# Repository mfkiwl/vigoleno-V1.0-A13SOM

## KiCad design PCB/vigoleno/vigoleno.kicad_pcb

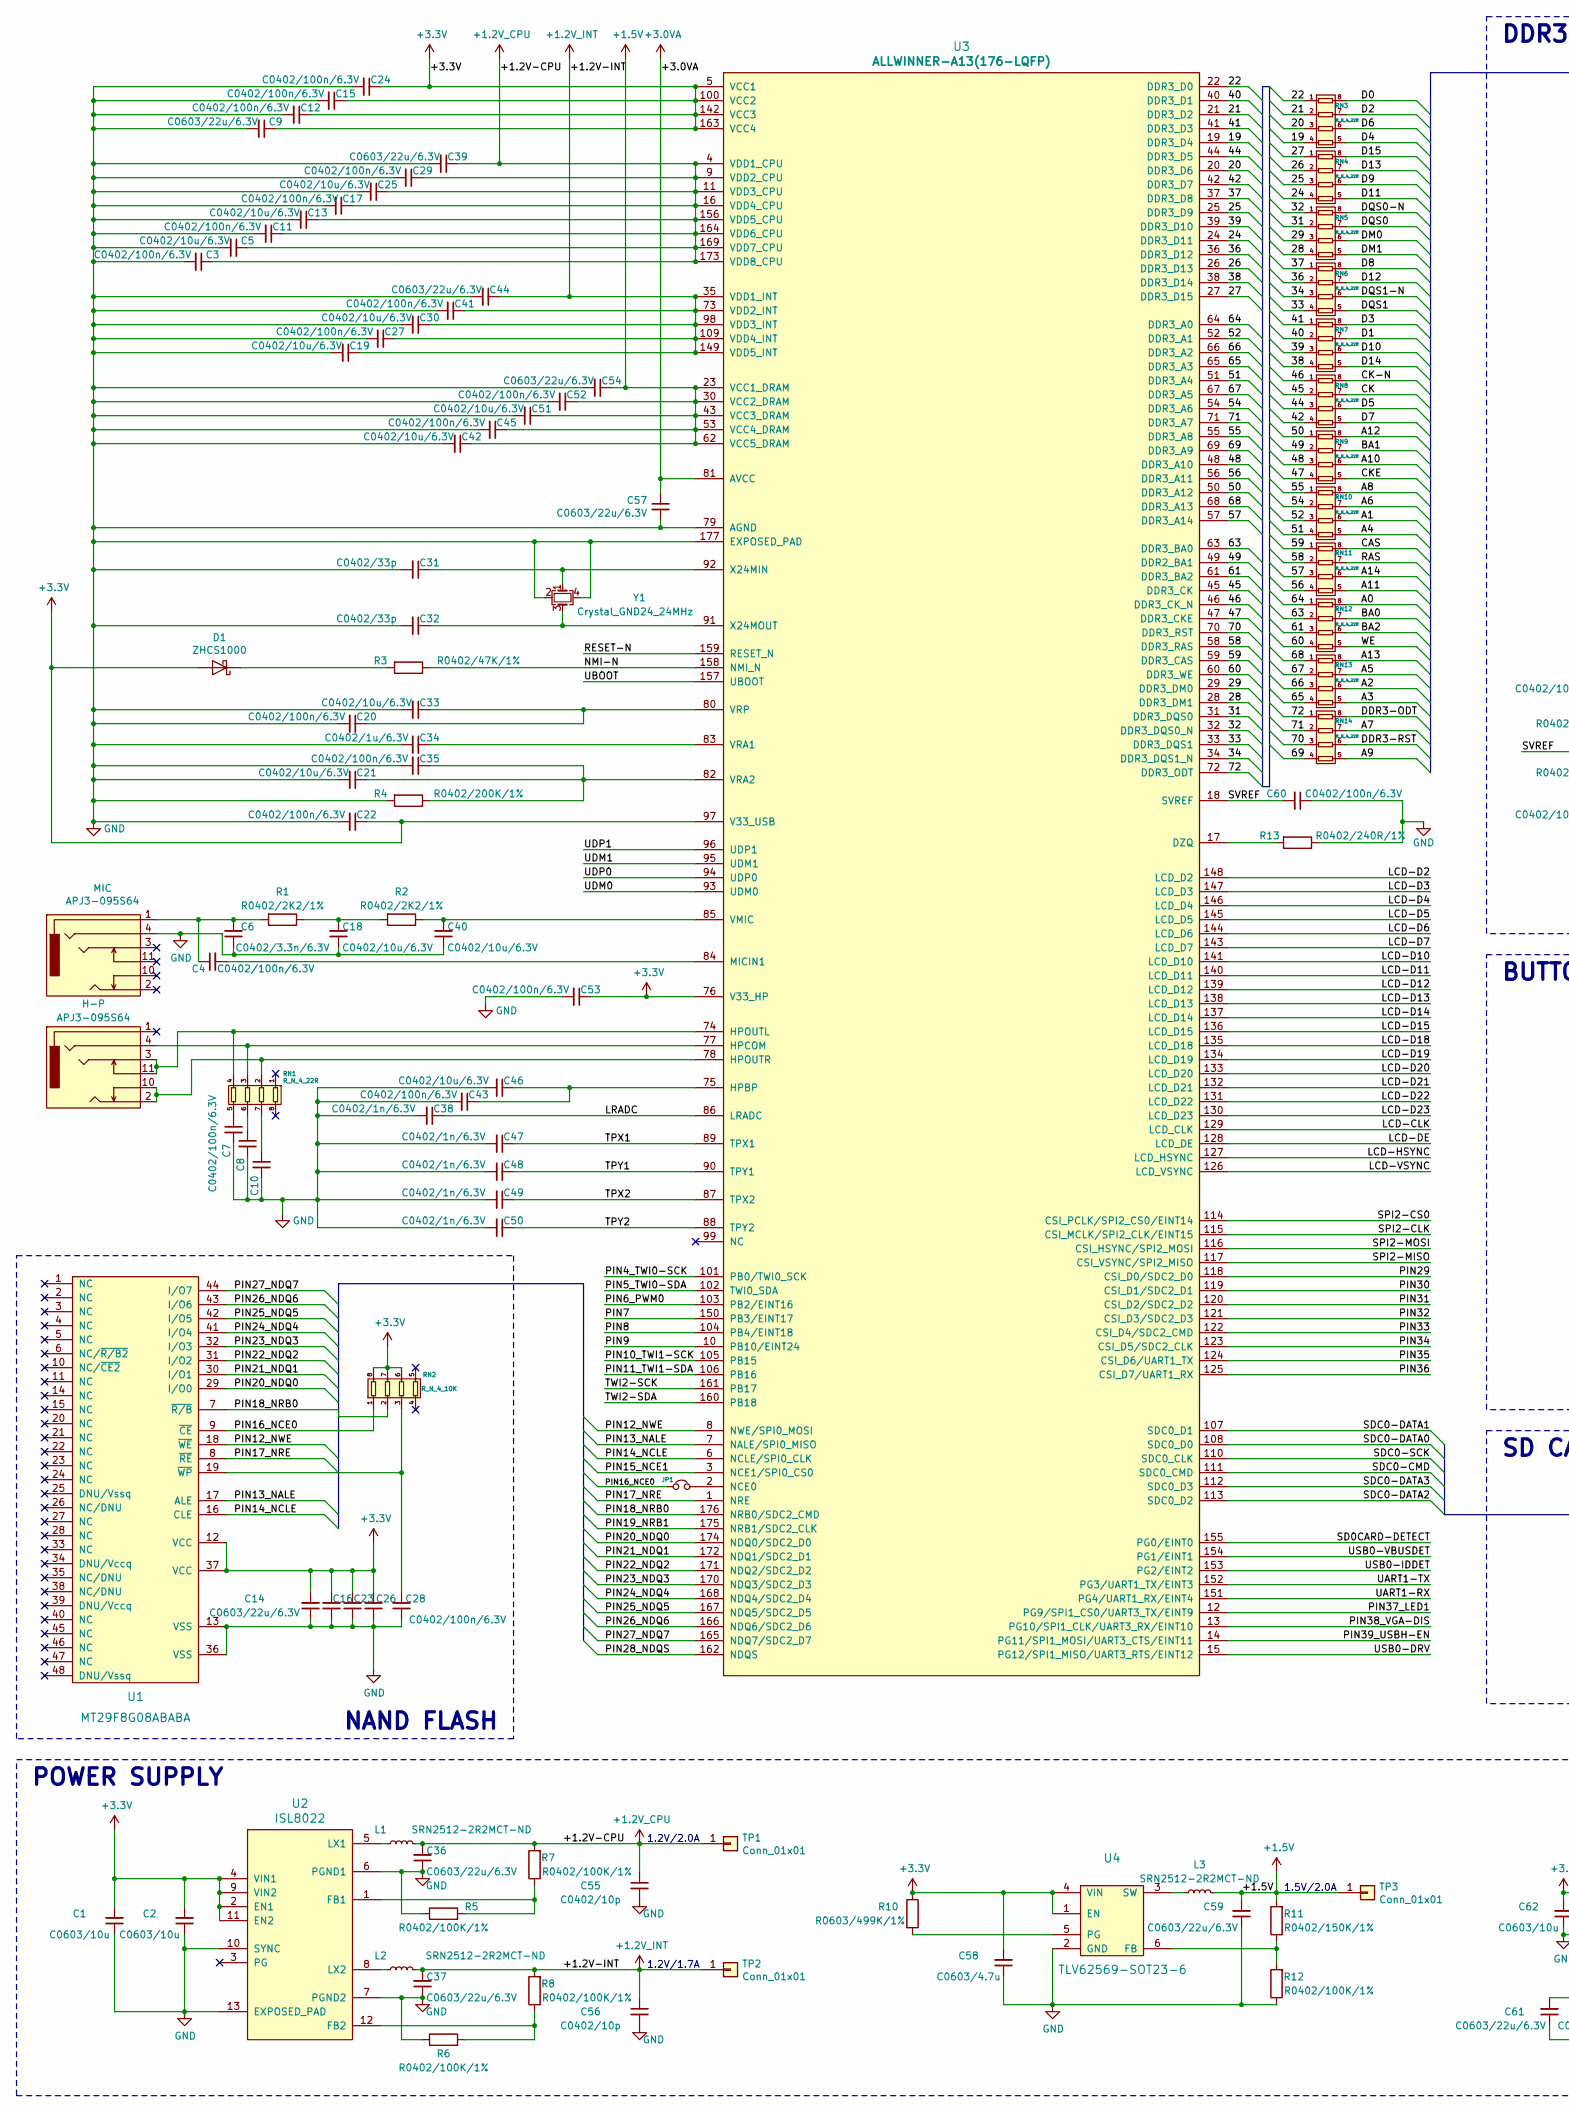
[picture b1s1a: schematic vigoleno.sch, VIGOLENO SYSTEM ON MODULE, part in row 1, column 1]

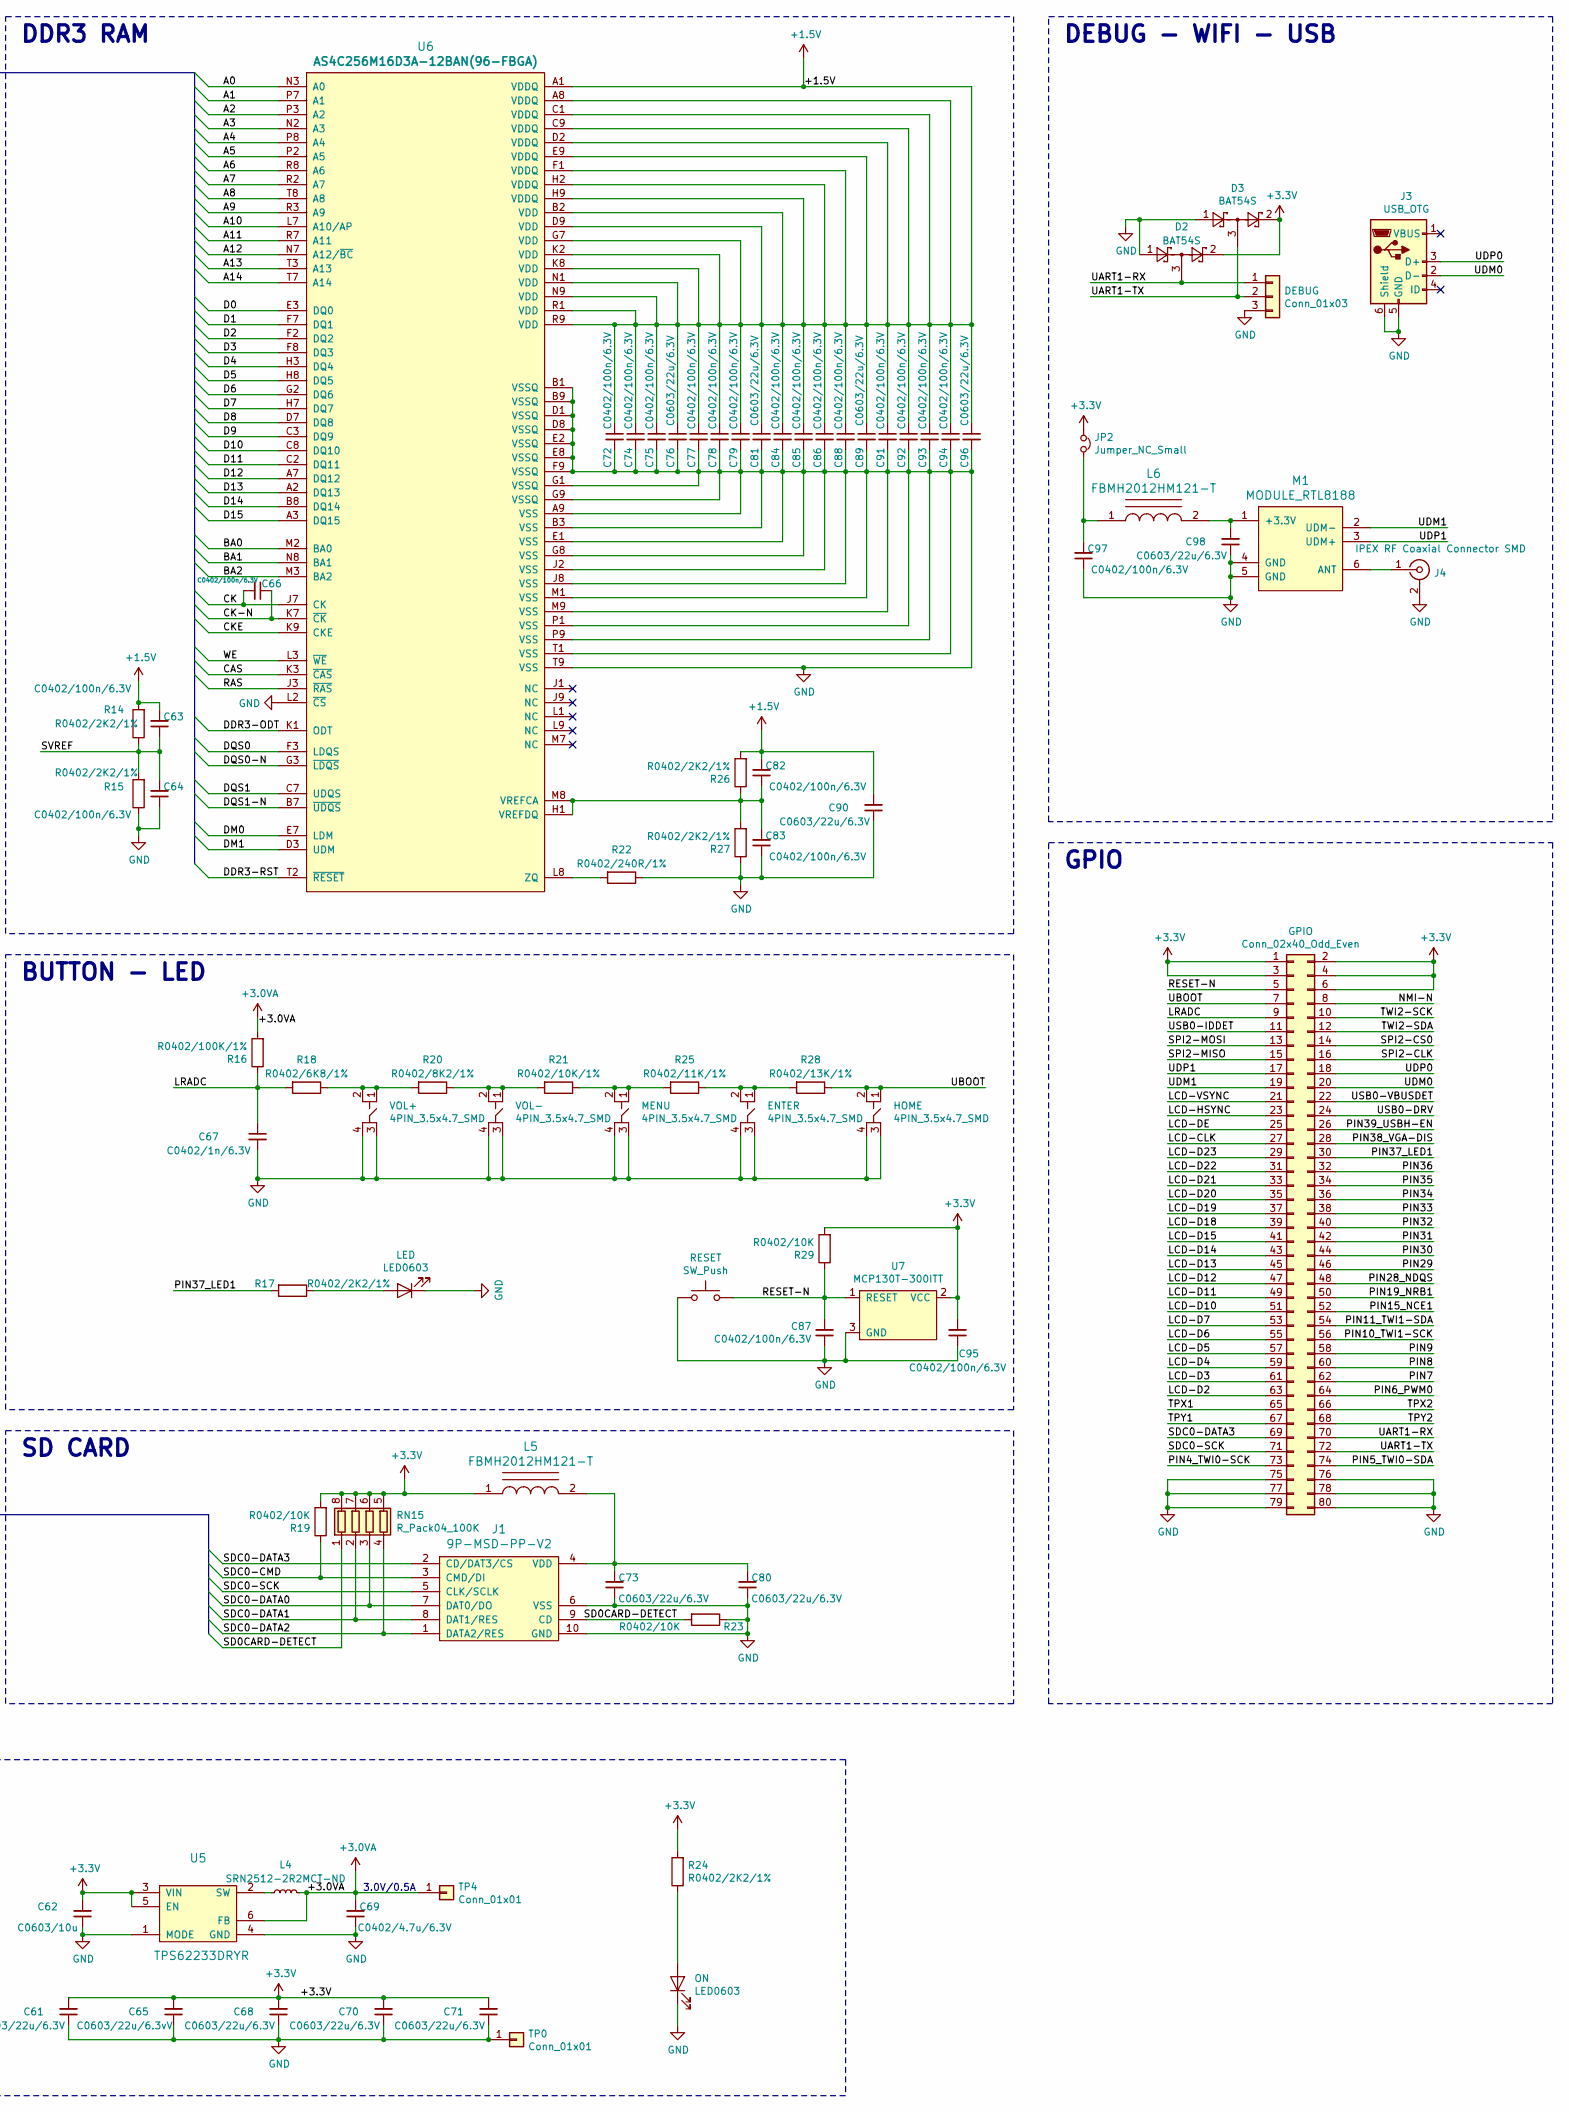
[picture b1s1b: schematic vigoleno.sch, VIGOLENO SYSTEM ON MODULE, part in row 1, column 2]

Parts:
C1, C2, C62: C0603/10u; C0603_HandSoldering
C3, C4, C7, C8, C10, C11, C12, C15, C16, C17, C20, C22, C23, C24, C26, C27, C28, C29, C35, C41, C43, C45, C52, C53, C60, C63, C64, C66, C72, C74, C75, C77, C78, C79, C82, C83, C84, C85, C86, C87, C88, C91, C92, C93, C94, C95, C97: C0402/100n/6.3V; C0402_HandSoldering
C5, C13, C18, C19, C21, C25, C30, C33, C40, C42, C46, C51: C0402/10u/6.3V; C0402_HandSoldering
C6: C0402/3.3n/6.3V; C0402_HandSoldering
C9, C14, C36, C37, C39, C44, C54, C57, C59, C61, C68, C70, C71, C73, C76, C80, C81, C89, C90, C96, C98: C0603/22u/6.3V; C0603_HandSoldering
C31, C32: C0402/33p; C0402_HandSoldering
C34: C0402/1u/6.3V; C0402_HandSoldering
C38, C47, C48, C49, C50, C67: C0402/1n/6.3V; C0402_HandSoldering
C55, C56: C0402/10p; C0402_HandSoldering
C58: C0603/4.7u; C0603_HandSoldering
C65: C0603/22u/6.3vV; C0603_HandSoldering
C69: C0402/4.7u/6.3V; C0402_HandSoldering
D1: ZHCS1000; SOT-23
D2, D3: BAT54S; SOT-23
DEBUG: Conn_01x03; Molex_CLIK-Mate_502585-0370_1x03-1MP_P1.50mm_Horizontal
ENTER: 4PIN_3.5x4.7_SMD
GPIO: Conn_02x40_Odd_Even; 2x40_pitch 0.8mm_SMD_header
H-P: APJ3-095S64; APJ3-095S64(Board_Cutout)
HOME: 4PIN_3.5x4.7_SMD
J1: 9P-MSD-PP-V2; MicroSD_9Pin_MSD-PP-V2
J3: USB_OTG; USB_Micro_3MV2
J4: IPEX RF Coaxial Connector SMD; U.FL_Hirose_U.FL-R-SMT-1_Vertical
JP1, JP2: Jumper_NC_Small; SolderJumper-2_P1.3mm_Open_TrianglePad1.0x1.5mm
L1, L2, L3, L4: SRN2512-2R2MCT-ND; Inductor_SRN2512_Series
L5, L6: FBMH2012HM121-T; L_0805_2012Metric
LED: LED0603; LED_0603_1608Metric
M1: MODULE_RTL8188; RTL8188_MODULE
MENU: 4PIN_3.5x4.7_SMD
MIC: APJ3-095S64; APJ3-095S64(Board_Cutout)
ON: LED0603; LED_0603_1608Metric
R1, R2, R14, R15, R17, R24, R26, R27: R0402/2K2/1%; R0402_HandSoldering
R3: R0402/47K/1%; R0402_HandSoldering
R4: R0402/200K/1%; R0402_HandSoldering
R5, R6, R7, R8, R12, R16: R0402/100K/1%; R0402_HandSoldering
R10: R0603/499K/1%; R0603_HandSoldering
R11: R0402/150K/1%; R0402_HandSoldering
R13, R22: R0402/240R/1%; R0402_HandSoldering
R18: R0402/6K8/1%; R0402_HandSoldering
R19, R23, R29: R0402/10K; R0402_HandSoldering
R20: R0402/8K2/1%; R0402_HandSoldering
R21: R0402/10K/1%; R0402_HandSoldering
R25: R0402/11K/1%; R0402_HandSoldering
R28: R0402/13K/1%; R0402_HandSoldering
RESET: SW_Push; SW_3x6x5_2Pin_SMD
RN1, RN3, RN4, RN5, RN6, RN7, RN8, RN9, RN10, RN11, RN12, RN13, RN14: R_N_4_22R; R_Array_0804_Convex_4x0402
RN2: R_N_4_10K; R_Array_0804_Convex_4x0402
RN15: R_Pack04_100K; R_Array_Convex_4x0603
TP0, TP1, TP2, TP3, TP4: Conn_01x01; TestPoint_Pad_D1.0mm
U1: MT29F8G08ABABA; S34ML08G2(48-TSOP)
U2: ISL8022; DFN-12-1EP_3x4mm_P0.5mm_EP1.7x3.3mm
U3: ALLWINNER-A13(176-LQFP); AllWinner-A13(176-LQFP)
U4: TLV62569-SOT23-6; SOT-23-6
U5: TPS62233DRYR; TPS62233DRYR_6_UFDFN
U6: AS4C256M16D3A-12BAN(96-FBGA)
U7: MCP130T-300ITT; SOT-23
VOL+: 4PIN_3.5x4.7_SMD
VOL-: 4PIN_3.5x4.7_SMD
Y1: Crystal_GND24_24MHz; Crystal_SMD_SeikoEpson_TSX3225-4pin_3.2x2.5mm_HandSoldering

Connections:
+3V3: C1.2, C2.2, C9.1, C12.1, C14.2, C15.1, C16.2, C22.1, C23.2, C24.1, C26.2, C53.1, C58.2, C61.2, C62.2, C65.2, C68.2, C70.2, C71.2, C95.2, D1.1 (A), D2.2, D3.2, GPIO.1, GPIO.2, GPIO.3, GPIO.4, GPIO.6, JP2.1, L5.1, R10.1, R19.2, R24.2, R29.2, RN2.6, RN2.7, RN2.8, RN15.5 (R4.2), RN15.6 (R3.2), RN15.7 (R2.2), RN15.8 (R1.2), U1.12 (VCC), U1.37 (VCC), U2.2 (EN1), U2.4 (VIN1), U2.9 (VIN2), U2.11 (EN2), U3.5 (VCC1), U3.76 (V33_HP), U3.97 (V33_USB), U3.100 (VCC2), U3.142 (VCC3), U3.163 (VCC4), U4.1 (EN), U4.4 (VIN), U5.3 (VIN), U5.5 (EN), U7.2 (VCC)
/19: RN3.4, U3.19 (DDR3_D4)
/20: RN3.3, U3.20 (DDR3_D6)
/21: RN3.2, U3.21 (DDR3_D2)
/22: RN3.1, U3.22 (DDR3_D0)
/24: RN4.4, U3.24 (DDR3_D11)
/25: RN4.3, U3.25 (DDR3_D9)
/26: RN4.2, U3.26 (DDR3_D13)
/27: RN4.1, U3.27 (DDR3_D15)
/28: RN5.4, U3.28 (DDR3_DM1)
/29: RN5.3, U3.29 (DDR3_DM0)
/31: RN5.2, U3.31 (DDR3_DQS0)
/32: RN5.1, U3.32 (DDR3_DQS0_N)
/33: RN6.4, U3.33 (DDR3_DQS1)
/34: RN6.3, U3.34 (DDR3_DQS1_N)
/36: RN6.2, U3.36 (DDR3_D12)
/37: RN6.1, U3.37 (DDR3_D8)
/38: RN7.4, U3.38 (DDR3_D14)
/39: RN7.3, U3.39 (DDR3_D10)
/40: RN7.2, U3.40 (DDR3_D1)
/41: RN7.1, U3.41 (DDR3_D3)
/42: RN8.4, U3.42 (DDR3_D7)
/44: RN8.3, U3.44 (DDR3_D5)
/45: RN8.2, U3.45 (DDR3_CK)
/46: RN8.1, U3.46 (DDR3_CK_N)
/47: RN9.4, U3.47 (DDR3_CKE)
/48: RN9.3, U3.48 (DDR3_A10)
/49: RN9.2, U3.49 (DDR2_BA1)
/50: RN9.1, U3.50 (DDR3_A12)
/51: RN10.4, U3.51 (DDR3_A4)
/52: RN10.3, U3.52 (DDR3_A1)
/54: RN10.2, U3.54 (DDR3_A6)
/55: RN10.1, U3.55 (DDR3_A8)
/56: RN11.4, U3.56 (DDR3_A11)
/57: RN11.3, U3.57 (DDR3_A14)
/58: RN11.2, U3.58 (DDR3_RAS)
/59: RN11.1, U3.59 (DDR3_CAS)
/60: RN12.4, U3.60 (DDR3_WE)
/61: RN12.3, U3.61 (DDR3_BA2)
/63: RN12.2, U3.63 (DDR3_BA0)
/64: RN12.1, U3.64 (DDR3_A0)
/65: RN13.4, U3.65 (DDR3_A3)
/66: RN13.3, U3.66 (DDR3_A2)
/67: RN13.2, U3.67 (DDR3_A5)
/68: RN13.1, U3.68 (DDR3_A13)
/69: RN14.4, U3.69 (DDR3_A9)
/70: RN14.3, U3.70 (DDR3_RST)
/71: RN14.2, U3.71 (DDR3_A7)
/72: RN14.1, U3.72 (DDR3_ODT)
/+1.2V-CPU: C3.1, C5.1, C11.1, C13.1, C17.1, C25.1, C29.1, C36.2, C39.1, C55.1, L1.2, R7.2, TP1.1, U3.4 (VDD1_CPU), U3.9 (VDD2_CPU), U3.11 (VDD3_CPU), U3.16 (VDD4_CPU), U3.156 (VDD5_CPU), U3.164 (VDD6_CPU), U3.169 (VDD7_CPU), U3.173 (VDD8_CPU)
/+1.2V-INT: C19.1, C27.1, C30.1, C37.2, C41.1, C44.1, C56.1, L2.2, R8.2, TP2.1, U3.35 (VDD1_INT), U3.73 (VDD2_INT), U3.98 (VDD3_INT), U3.109 (VDD4_INT), U3.149 (VDD5_INT)
/+3.0VA: C57.1, C69.2, L4.2, R16.2, TP4.1, U3.81 (AVCC), U5.6 (FB)
/A0: RN12.8, U6.N3 (A0)
/A1: RN10.6, U6.P7 (A1)
/A2: RN13.6, U6.P3 (A2)
/A3: RN13.5, U6.N2 (A3)
/A4: RN10.5, U6.P8 (A4)
/A5: RN13.7, U6.P2 (A5)
/A6: RN10.7, U6.R8 (A6)
/A7: RN14.7, U6.R2 (A7)
/A8: RN10.8, U6.T8 (A8)
/A9: RN14.5, U6.R3 (A9)
/A10: RN9.6, U6.L7 (A10/AP)
/A11: RN11.5, U6.R7 (A11)
/A12: RN9.8, U6.N7 (A12/~BC)
/A13: RN13.8, U6.T3 (A13)
/A14: RN11.6, U6.T7 (A14)
/BA0: RN12.7, U6.M2 (BA0)
/BA1: RN9.7, U6.N8 (BA1)
/BA2: RN12.6, U6.M3 (BA2)
/CAS: RN11.8, U6.K3 (~CAS)
/CK: C66.2, RN8.7, U6.J7 (CK)
/CK-N: C66.1, RN8.8, U6.K7 (~CK)
/CKE: RN9.5, U6.K9 (CKE)
/D0: RN3.8, U6.E3 (DQ0)
/D1: RN7.7, U6.F7 (DQ1)
/D2: RN3.7, U6.F2 (DQ2)
/D3: RN7.8, U6.F8 (DQ3)
/D4: RN3.5, U6.H3 (DQ4)
/D5: RN8.6, U6.H8 (DQ5)
/D6: RN3.6, U6.G2 (DQ6)
/D7: RN8.5, U6.H7 (DQ7)
/D8: RN6.8, U6.D7 (DQ8)
/D9: RN4.6, U6.C3 (DQ9)
/D10: RN7.6, U6.C8 (DQ10)
/D11: RN4.5, U6.C2 (DQ11)
/D12: RN6.7, U6.A7 (DQ12)
/D13: RN4.7, U6.A2 (DQ13)
/D14: RN7.5, U6.B8 (DQ14)
/D15: RN4.8, U6.A3 (DQ15)
/DDR3-ODT: RN14.8, U6.K1 (ODT)
/DDR3-RST: RN14.6, U6.T2 (~RESET)
/DM0: RN5.6, U6.E7 (LDM)
/DM1: RN5.5, U6.D3 (UDM)
/DQS0: RN5.7, U6.F3 (LDQS)
/DQS0-N: RN5.8, U6.G3 (~LDQS)
/DQS1: RN6.5, U6.C7 (UDQS)
/DQS1-N: RN6.6, U6.B7 (~UDQS)
/LCD-CLK: GPIO.27, U3.129 (LCD_CLK)
/LCD-D2: GPIO.63, U3.148 (LCD_D2)
/LCD-D3: GPIO.61, U3.147 (LCD_D3)
/LCD-D4: GPIO.59, U3.146 (LCD_D4)
/LCD-D5: GPIO.57, U3.145 (LCD_D5)
/LCD-D6: GPIO.55, U3.144 (LCD_D6)
/LCD-D7: GPIO.53, U3.143 (LCD_D7)
/LCD-D10: GPIO.51, U3.141 (LCD_D10)
/LCD-D11: GPIO.49, U3.140 (LCD_D11)
/LCD-D12: GPIO.47, U3.139 (LCD_D12)
/LCD-D13: GPIO.45, U3.138 (LCD_D13)
/LCD-D14: GPIO.43, U3.137 (LCD_D14)
/LCD-D15: GPIO.41, U3.136 (LCD_D15)
/LCD-D18: GPIO.39, U3.135 (LCD_D18)
/LCD-D19: GPIO.37, U3.134 (LCD_D19)
/LCD-D20: GPIO.35, U3.133 (LCD_D20)
/LCD-D21: GPIO.33, U3.132 (LCD_D21)
/LCD-D22: GPIO.31, U3.131 (LCD_D22)
/LCD-D23: GPIO.29, U3.130 (LCD_D23)
/LCD-DE: GPIO.25, U3.128 (LCD_DE)
/LCD-HSYNC: GPIO.23, U3.127 (LCD_HSYNC)
/LCD-VSYNC: GPIO.21, U3.126 (LCD_VSYNC)
/LRADC: C38.1, C67.1, GPIO.9, R16.1, R18.2, U3.86 (LRADC)
/NMI-N: GPIO.8, R3.1, U3.158 (NMI_N)
/PIN4_TWI0-SCK: GPIO.73, U3.101 (PB0/TWI0_SCK)
/PIN5_TWI0-SDA: GPIO.74, U3.102 (TWI0_SDA)
/PIN6_PWM0: GPIO.64, U3.103 (PB2/EINT16)
/PIN7: GPIO.62, U3.150 (PB3/EINT17)
/PIN8: GPIO.60, U3.104 (PB4/EINT18)
/PIN9: GPIO.58, U3.10 (PB10/EINT24)
/PIN10_TWI1-SCK: GPIO.56, U3.105 (PB15)
/PIN11_TWI1-SDA: GPIO.54, U3.106 (PB16)
/PIN12_NWE: U1.18 (~WE), U3.8 (NWE/SPI0_MOSI)
/PIN13_NALE: U1.17 (ALE), U3.7 (NALE/SPI0_MISO)
/PIN14_NCLE: U1.16 (CLE), U3.6 (NCLE/SPI0_CLK)
/PIN15_NCE1: GPIO.52, U3.3 (NCE1/SPI0_CS0)
/PIN16_NCE0: JP1.1, RN2.1, U1.9 (~CE)
/PIN17_NRE: U1.8 (~RE), U3.1 (NRE)
/PIN18_NRB0: RN2.2, U1.7 (~R/B), U3.176 (NRB0/SDC2_CMD)
/PIN19_NRB1: GPIO.50, U3.175 (NRB1/SDC2_CLK)
/PIN20_NDQ0: U1.29 (I/O0), U3.174 (NDQ0/SDC2_D0)
/PIN21_NDQ1: U1.30 (I/O1), U3.172 (NDQ1/SDC2_D1)
/PIN22_NDQ2: U1.31 (I/O2), U3.171 (NDQ2/SDC2_D2)
/PIN23_NDQ3: U1.32 (I/O3), U3.170 (NDQ3/SDC2_D3)
/PIN24_NDQ4: U1.41 (I/O4), U3.168 (NDQ4/SDC2_D4)
/PIN25_NDQ5: U1.42 (I/O5), U3.167 (NDQ5/SDC2_D5)
/PIN26_NDQ6: U1.43 (I/O6), U3.166 (NDQ6/SDC2_D6)
/PIN27_NDQ7: U1.44 (I/O7), U3.165 (NDQ7/SDC2_D7)
/PIN28_NDQS: GPIO.48, U3.162 (NDQS)
/PIN29: GPIO.46, U3.118 (CSI_D0/SDC2_D0)
/PIN30: GPIO.44, U3.119 (CSI_D1/SDC2_D1)
/PIN31: GPIO.42, U3.120 (CSI_D2/SDC2_D2)
/PIN32: GPIO.40, U3.121 (CSI_D3/SDC2_D3)
/PIN33: GPIO.38, U3.122 (CSI_D4/SDC2_CMD)
/PIN34: GPIO.36, U3.123 (CSI_D5/SDC2_CLK)
/PIN35: GPIO.34, U3.124 (CSI_D6/UART1_TX)
/PIN36: GPIO.32, U3.125 (CSI_D7/UART1_RX)
/PIN37_LED1: GPIO.30, R17.2, U3.12 (PG9/SPI1_CS0/UART3_TX/EINT9)
/PIN38_VGA-DIS: GPIO.28, U3.13 (PG10/SPI1_CLK/UART3_RX/EINT10)
/PIN39_USBH-EN: GPIO.26, U3.14 (PG11/SPI1_MOSI/UART3_CTS/EINT11)
/RAS: RN11.7, U6.J3 (~RAS)
/RESET-N: C87.2, GPIO.5, R29.1, RESET.2, U3.159 (RESET_N), U7.1 (RESET)
/SD0CARD-DETECT: J1.9 (CD), R23.2, RN15.1 (R1.1), U3.155 (PG0/EINT0)
/SDC0-CMD: J1.3 (CMD/DI), R19.1, U3.111 (SDC0_CMD)
/SDC0-DATA0: J1.7 (DAT0/DO), RN15.3 (R3.1), U3.108 (SDC0_D0)
/SDC0-DATA1: J1.8 (DAT1/RES), RN15.2 (R2.1), U3.107 (SDC0_D1)
/SDC0-DATA2: J1.1 (DATA2/RES), RN15.4 (R4.1), U3.113 (SDC0_D2)
/SDC0-DATA3: GPIO.69, J1.2 (CD/DAT3/CS), U3.112 (SDC0_D3)
/SDC0-SCK: GPIO.71, J1.5 (CLK/SCLK), U3.110 (SDC0_CLK)
/SPI2-CLK: GPIO.16, U3.115 (CSI_MCLK/SPI2_CLK/EINT15)
/SPI2-CS0: GPIO.14, U3.114 (CSI_PCLK/SPI2_CS0/EINT14)
/SPI2-MISO: GPIO.15, U3.117 (CSI_VSYNC/SPI2_MISO)
/SPI2-MOSI: GPIO.13, U3.116 (CSI_HSYNC/SPI2_MOSI)
/SVREF: C60.2, C63.1, C64.2, R14.1, R15.2, U3.18 (SVREF)
/TPX1: C47.1, GPIO.65, U3.89 (TPX1)
/TPX2: C49.1, GPIO.66, U3.87 (TPX2)
/TPY1: C48.1, GPIO.67, U3.90 (TPY1)
/TPY2: C50.1, GPIO.68, U3.88 (TPY2)
/TWI2-SCK: GPIO.10, U3.161 (PB17)
/TWI2-SDA: GPIO.12, U3.160 (PB18)
/UART1-RX: D2.3, DEBUG.1, GPIO.70, U3.151 (PG4/UART1_RX/EINT4)
/UART1-TX: D3.3, DEBUG.2, GPIO.72, U3.152 (PG3/UART1_TX/EINT3)
/UBOOT: GPIO.7, HOME.1 (A), HOME.2 (B), R28.1, U3.157 (UBOOT)
/UDM0: GPIO.20, J3.2 (D-), U3.93 (UDM0)
/UDM1: GPIO.19, M1.2 (UDM-), U3.95 (UDM1)
/UDP0: GPIO.18, J3.3 (D+), U3.94 (UDP0)
/UDP1: GPIO.17, M1.3 (UDM+), U3.96 (UDP1)
/USB0-DRV: GPIO.24, U3.15 (PG12/SPI1_MISO/UART3_RTS/EINT12)
/USB0-IDDET: GPIO.11, U3.153 (PG2/EINT2)
/USB0-VBUSDET: GPIO.22, U3.154 (PG1/EINT1)
/WE: RN12.5, U6.L3 (~WE)
GND: C1.1, C2.1, C3.2, C5.2, C7.2, C8.2, C9.2, C10.2, C11.2, C12.2, C13.2, C14.1, C15.2, C16.1, C17.2, C18.1, C19.2, C20.2, C21.2, C22.2, C23.1, C24.2, C25.2, C26.1, C27.2, C28.1, C29.2, C30.2, C31.2, C32.2, C33.2, C34.2, C35.2, C36.1, C37.1, C38.2, C39.2, C40.1, C41.2, C42.2, C43.2, C44.2, C45.2, C46.2, C47.2, C48.2, C49.2, C50.2, C51.2, C52.2, C53.2, C54.2, C55.2, C56.2, C57.2, C58.1, C59.1, C60.1, C61.1, C62.1, C64.1, C65.1, C67.2, C68.1, C69.1, C70.1, C71.1, C72.2, C73.1, C74.2, C75.2, C76.2, C77.2, C78.2, C79.2, C80.1, C81.2, C83.1, C84.2, C85.2, C86.2, C87.1, C88.2, C89.2, C90.1, C91.2, C92.2, C93.2, C94.2, C95.1, C96.2, C97.1, C98.1, D2.1, D3.1, DEBUG.3, ENTER.3 (C), ENTER.4 (D), GPIO.75, GPIO.76, GPIO.77, GPIO.78, GPIO.79, GPIO.80, HOME.3 (C), HOME.4 (D), J1.6 (VSS), J1.10 (GND), J3.5 (GND), J3.6 (Shield), J4.2 (Ext), LED.1 (K), M1.4 (GND), M1.5 (GND), MENU.3 (C), MENU.4 (D), MIC.4, ON.1 (K), R4.2, R5.1, R6.1, R12.1, R13.1, R15.1, R22.1, R23.1, R27.1, RESET.1, TP0.1, U1.13 (VSS), U1.36 (VSS), U2.6 (PGND1), U2.7 (PGND2), U2.10 (SYNC), U2.13 (EXPOSED_PAD), U3.79 (AGND), U3.177 (EXPOSED_PAD), U4.2 (GND), U5.1 (MODE), U5.4 (GND), U6.A9 (VSS), U6.B1 (VSSQ), U6.B3 (VSS), U6.B9 (VSSQ), U6.D1 (VSSQ), U6.D8 (VSSQ), U6.E1 (VSS), U6.E2 (VSSQ), U6.E8 (VSSQ), U6.F9 (VSSQ), U6.G1 (VSSQ), U6.G8 (VSS), U6.G9 (VSSQ), U6.J2 (VSS), U6.J8 (VSS), U6.L2 (~CS), U6.M1 (VSS), U6.M9 (VSS), U6.P1 (VSS), U6.P9 (VSS), U6.T1 (VSS), U6.T9 (VSS), U7.3 (GND), VOL+.3 (C), VOL+.4 (D), VOL-.3 (C), VOL-.4 (D), Y1.2, Y1.4
unnamed: C4.1, C6.2, MIC.1, R1.2
unnamed: C4.2, U3.84 (MICIN1)
unnamed: C7.1, RN1.5
unnamed: C8.1, RN1.6
unnamed: C10.1, RN1.7
unnamed: C18.2, R1.1, R2.2
unnamed: C20.1, C33.1, U3.80 (VRP)
unnamed: C21.1, C35.1, R4.1, U3.82 (VRA2)
unnamed: C28.2, RN2.3, U1.19 (~WP)
unnamed: C31.1, U3.92 (X24MIN), Y1.1
unnamed: C32.1, U3.91 (X24MOUT), Y1.3
unnamed: C34.1, U3.83 (VRA1)
unnamed: C40.2, R2.1, U3.85 (VMIC)
unnamed: C43.1, C46.1, U3.75 (HPBP)
unnamed: C73.2, C80.2, J1.4 (VDD), L5.2
unnamed: C82.1, C83.2, R26.1, R27.2, U6.H1 (VREFDQ), U6.M8 (VREFCA)
unnamed: C97.2, JP2.2, L6.1
unnamed: C98.2, L6.2, M1.1 (+3.3V)
unnamed: D1.3 (K), R3.2
unnamed: ENTER.1 (A), ENTER.2 (B), R25.1, R28.2
unnamed: H-P.4, RN1.3, U3.77 (HPCOM)
unnamed: H-P.2, H-P.10, RN1.2, U3.78 (HPOUTR)
unnamed: H-P.3, H-P.11, RN1.4, U3.74 (HPOUTL)
unnamed: J4.1 (In), M1.6 (ANT)
unnamed: JP1.2, U3.2 (NCE0)
unnamed: L1.1, U2.5 (LX1)
unnamed: L2.1, U2.8 (LX2)
unnamed: L3.1, U4.3 (SW)
unnamed: L4.1, U5.2 (SW)
unnamed: LED.2 (A), R17.1
unnamed: MENU.1 (A), MENU.2 (B), R21.1, R25.2
unnamed: ON.2 (A), R24.1
unnamed: R5.2, R7.1, U2.1 (FB1)
unnamed: R6.2, R8.1, U2.12 (FB2)
unnamed: R10.2, U4.5 (PG)
unnamed: R11.1, R12.2, U4.6 (FB)
unnamed: R13.2, U3.17 (DZQ)
unnamed: R18.1, R20.2, VOL+.1 (A), VOL+.2 (B)
unnamed: R20.1, R21.2, VOL-.1 (A), VOL-.2 (B)
unnamed: R22.2, U6.L8 (ZQ)

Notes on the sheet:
1.2V/1.7A
1.2V/2.0A
1.5V/2.0A
3.0V/0.5A
DDR3 RAM
BUTTON - LED
SD CARD
GPIO
DEBUG - WIFI - USB
POWER SUPPLY
NAND FLASH

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
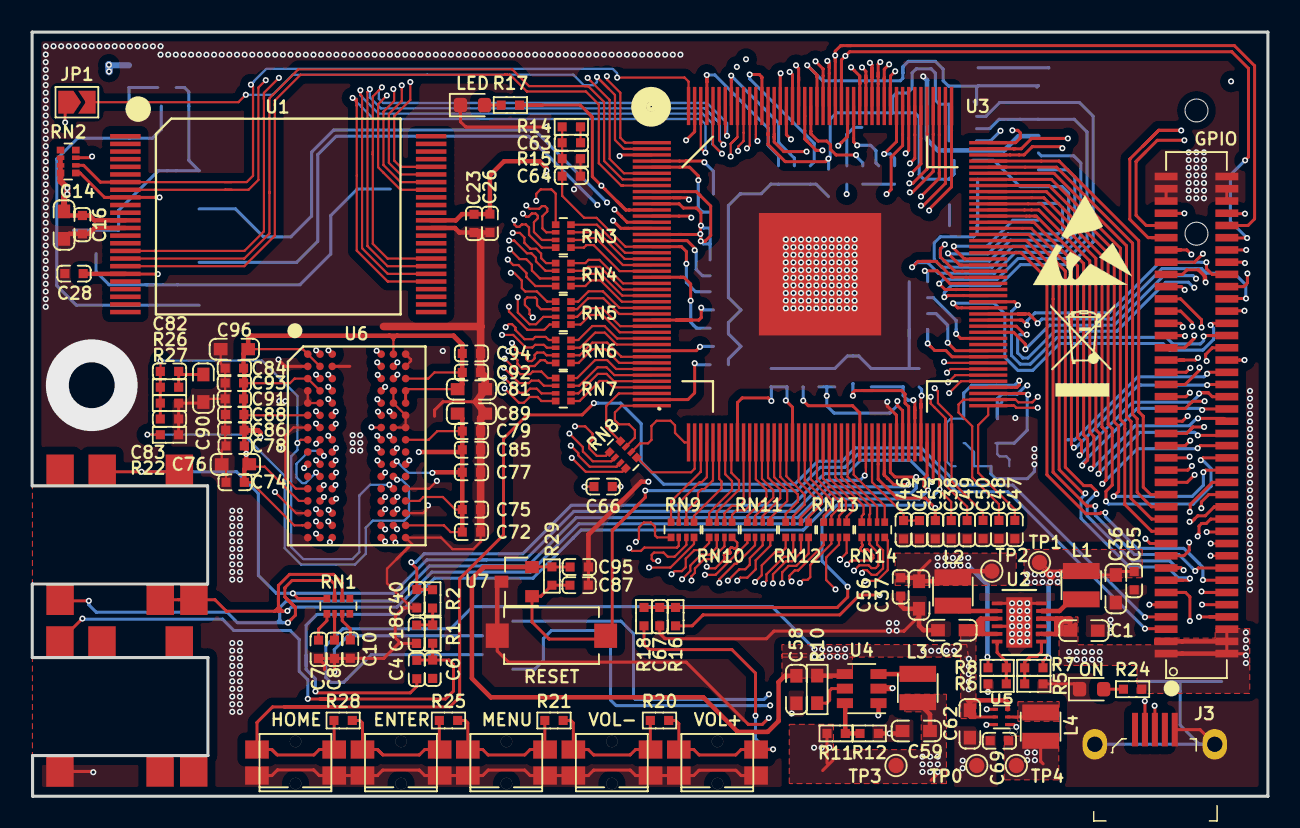
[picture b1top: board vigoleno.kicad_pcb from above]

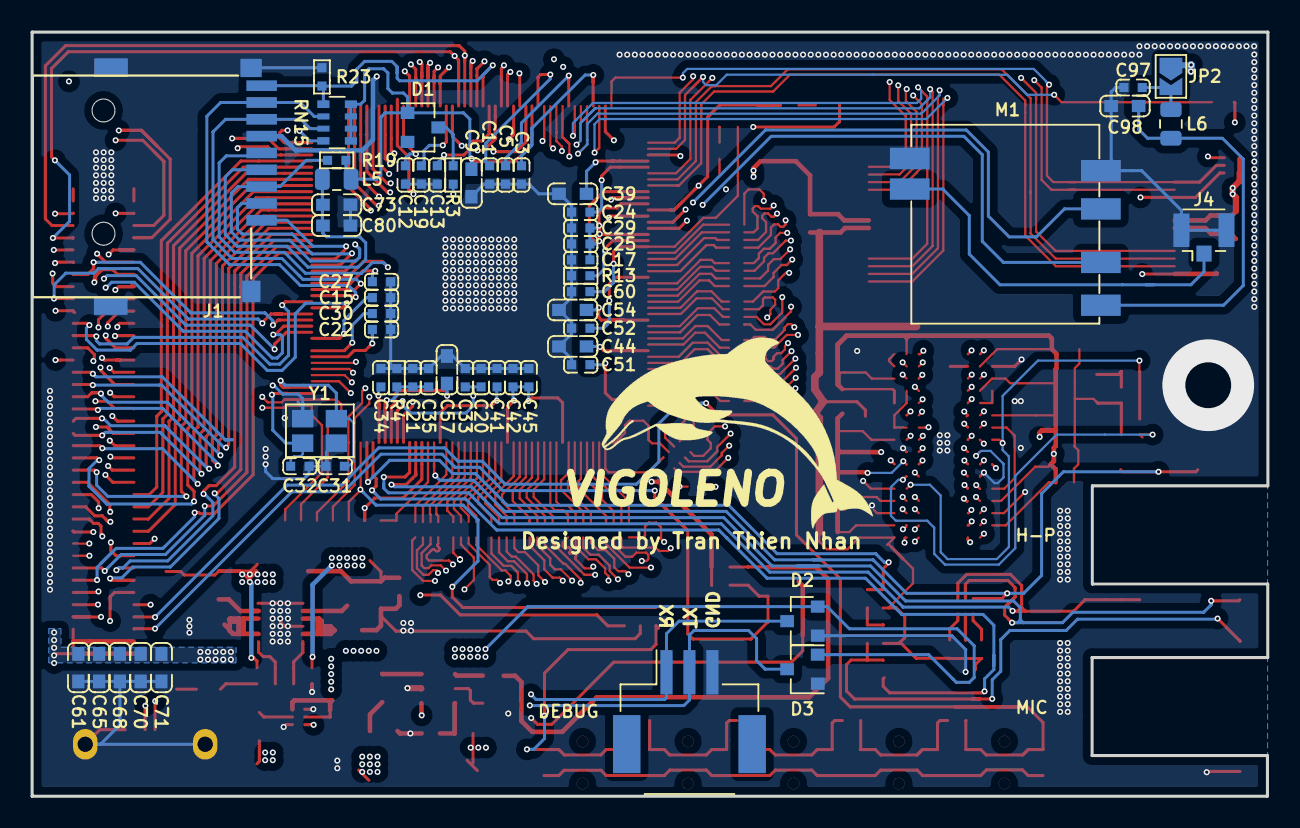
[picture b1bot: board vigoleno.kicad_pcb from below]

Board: 6 copper layers, 80.8 x 50.0 mm, 181 parts (60 on the bottom side), 233 nets.

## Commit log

2018-12-03 add schematic
2018-12-14 update Dec 14
2018-12-14 update Dec 14 2018
2018-12-15 update Dec 15 2018
2018-12-15 update RAM port
2018-12-17 update Dec 17 2018
2018-12-17 add new pcb file
2018-12-17 add pcb folder
2018-12-19 update vigoleno pcb
2018-12-19 update Dec 19 2018
2018-12-20 update Dec 20 2018
2018-12-21 update Dec 21 2018
2018-12-24 update Dec 24 2018
2018-12-25 update Dec 25 2018
2019-01-05 update JAN 5 2019
2019-01-06 update Jan 6 2019
2019-01-07 update Jan 7 2019
2019-01-08 update Documents file and Main board schematic
2019-01-08 update Jan 8 2019
2019-02-01 update Feb 1
2019-02-25 update Feb 25 2019
2019-02-27 update Feb 27
2019-03-05 update March 52019
2019-03-06 update March 6 2019
2019-08-09 finished VIGOLENO SBC PCB layout
